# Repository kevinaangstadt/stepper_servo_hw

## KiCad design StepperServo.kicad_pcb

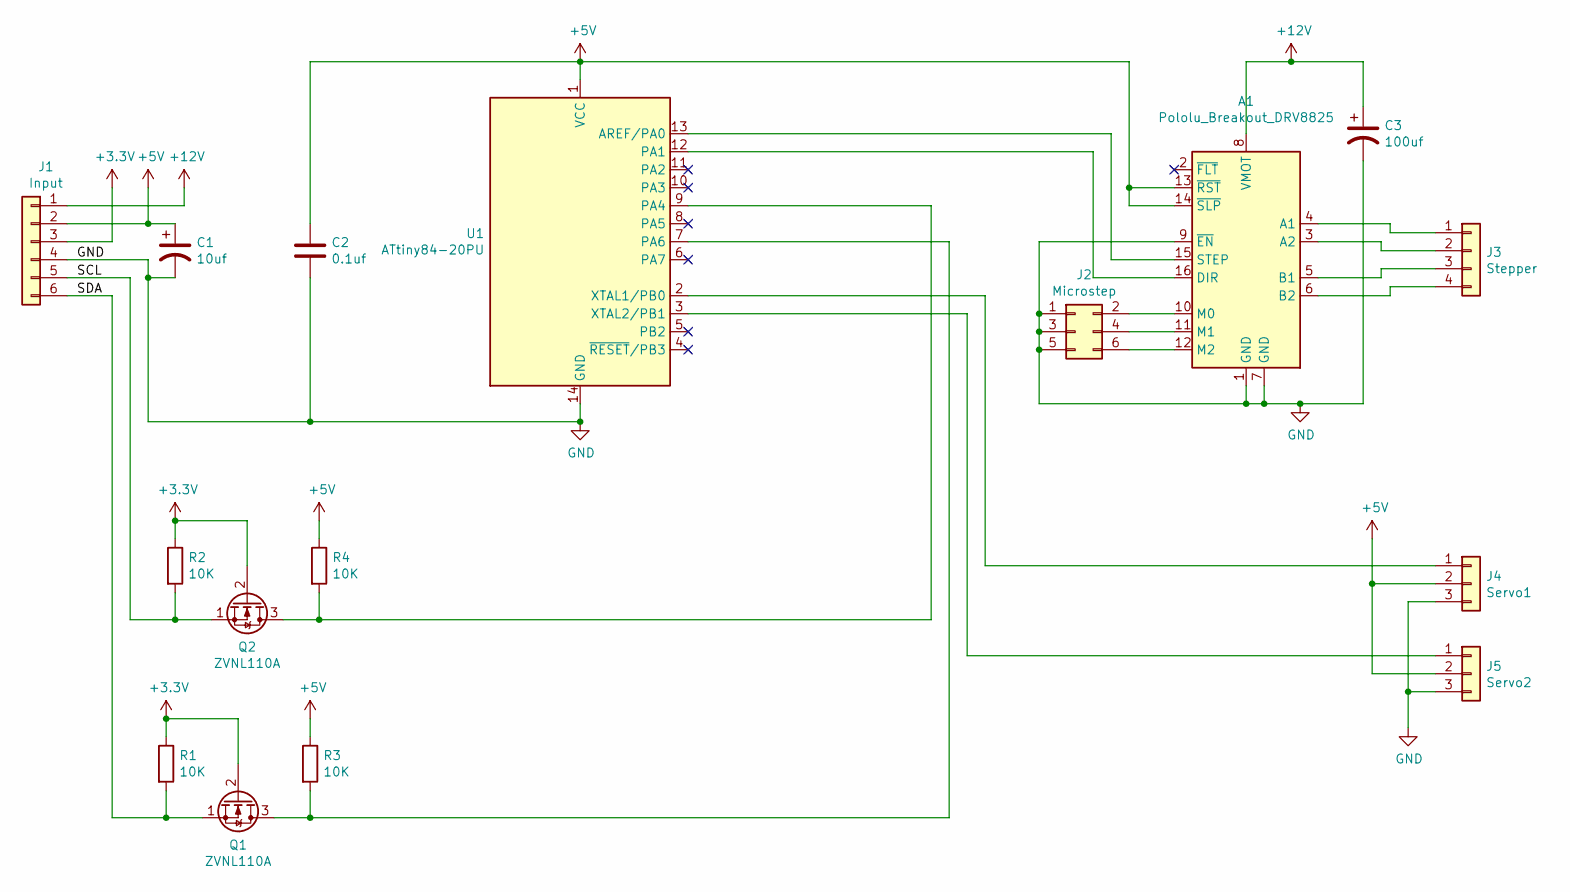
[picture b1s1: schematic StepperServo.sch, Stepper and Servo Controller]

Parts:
A1: Pololu_Breakout_DRV8825; Pololu_Breakout-16_15.2x20.3mm
C1: 10uf; CP_Radial_Tantal_D6.0mm_P2.50mm
C2: 0.1uf; C_Disc_D5.0mm_W2.5mm_P2.50mm
C3: 100uf; CP_Radial_D5.0mm_P2.50mm
J1: Input; PinHeader_1x06_P2.54mm_Vertical
J2: Microstep; PinHeader_2x03_P2.54mm_Vertical
J3: Stepper; PinHeader_1x04_P2.54mm_Vertical
J4: Servo1; PinHeader_1x03_P2.54mm_Vertical
J5: Servo2; PinHeader_1x03_P2.54mm_Vertical
Q1, Q2: ZVNL110A; TO-92_Inline_Wide
R1, R2, R3, R4: 10K; R_Axial_DIN0207_L6.3mm_D2.5mm_P2.54mm_Vertical
U1: ATtiny84-20PU; DIP-14_W7.62mm

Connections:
+3V3: J1.3, Q1.2 (G), Q2.2 (G), R1.1, R2.1
+5V: A1.13 (~RST), A1.14 (~SLP), C1.1, C2.1, J1.2, J4.2, J5.2, R3.1, R4.1, U1.1 (VCC)
+12V: A1.8 (VMOT), C3.1, J1.1
/SCL: J1.5, Q2.1 (S), R2.2
/SDA: J1.6, Q1.1 (S), R1.2
GND: A1.1 (GND), A1.7 (GND), A1.9 (~EN), C1.2, C2.2, C3.2, J1.4, J2.1, J2.3, J2.5, J4.3, J5.3, U1.14 (GND)
unnamed: A1.3 (A2), J3.2
unnamed: A1.4 (A1), J3.1
unnamed: A1.5 (B1), J3.3
unnamed: A1.6 (B2), J3.4
unnamed: A1.10 (M0), J2.2
unnamed: A1.11 (M1), J2.4
unnamed: A1.12 (M2), J2.6
unnamed: A1.15 (STEP), U1.13 (AREF/PA0)
unnamed: A1.16 (DIR), U1.12 (PA1)
unnamed: J4.1, U1.2 (XTAL1/PB0)
unnamed: J5.1, U1.3 (XTAL2/PB1)
unnamed: Q1.3 (D), R3.2, U1.7 (PA6)
unnamed: Q2.3 (D), R4.2, U1.9 (PA4)

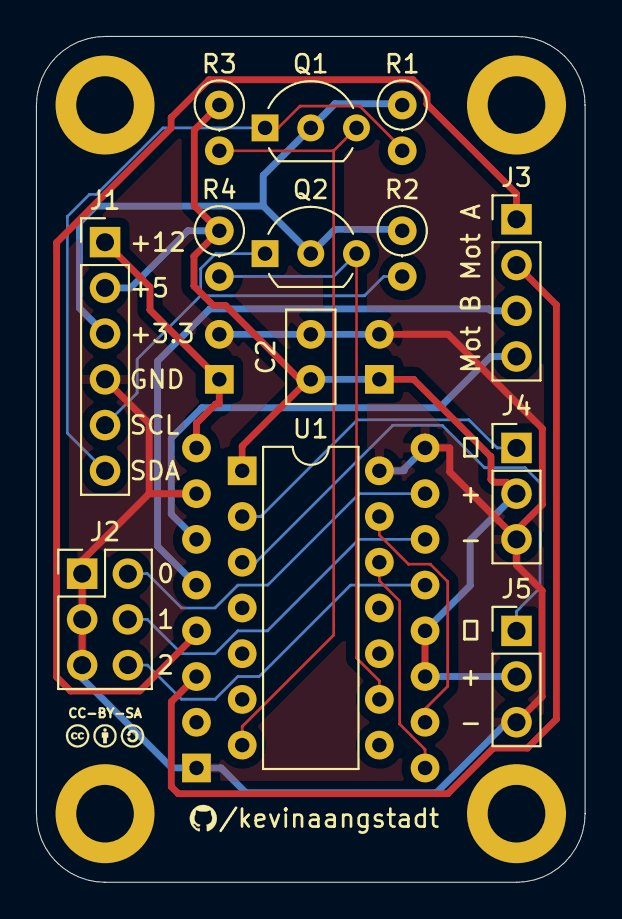
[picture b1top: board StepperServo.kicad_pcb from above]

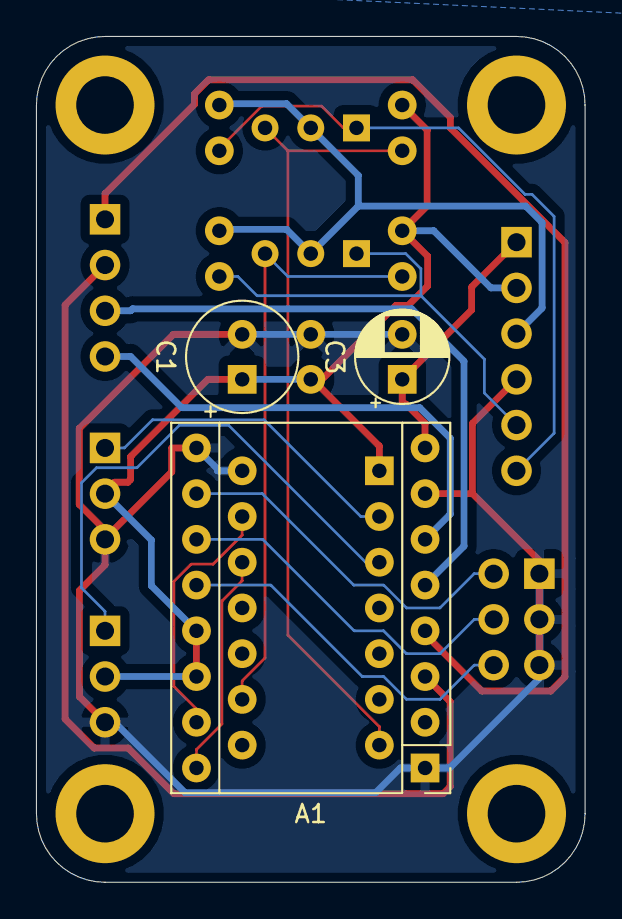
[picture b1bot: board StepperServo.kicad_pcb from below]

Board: 2 copper layers, 30.5 x 47.0 mm, 24 parts (3 on the bottom side), 19 nets.

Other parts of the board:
G1: LOGO; GitHub_tiny
G2: LOGO; Symbol_CC-_Silk_Tiny
G3: LOGO; Symbol_CC-Attribution_Silkscreen_Tiny
G4: LOGO; Symbol_CC-SA_Silk_Tiny
H1, H2, H3, H4: MountingHole_3.2mm_M3_ISO14580_Pad

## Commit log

2020-03-14 Initial schematic design
2020-03-14 Updated schematic
2020-03-14 Fixed tantalum and assigned footprints
2020-03-15 PCB Layout

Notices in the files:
StepperServo.kicad_pcb:
CC-BY-SA
StepperServo.sch:
CC BY-SA 4.0
